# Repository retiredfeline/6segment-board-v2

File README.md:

# 6 segment 2 digit board, second version

These are the Kicad design files for the second version of the [6 segment 2 digit board](https://hackaday.io/project/175397-6-segment-2-digit-led-board) project, explained in a [log](https://hackaday.io/project/175396-6-segments-suffice/log/202924-6-segments-reloaded) for the original project. Changes have been made to the segment shapes to attempt to improve the font.

## Versioning

Release February 2022

## Authors

* **Ken Yap**

## License

See the [LICENSE](LICENSE.md) file for license rights and limitations (MIT).

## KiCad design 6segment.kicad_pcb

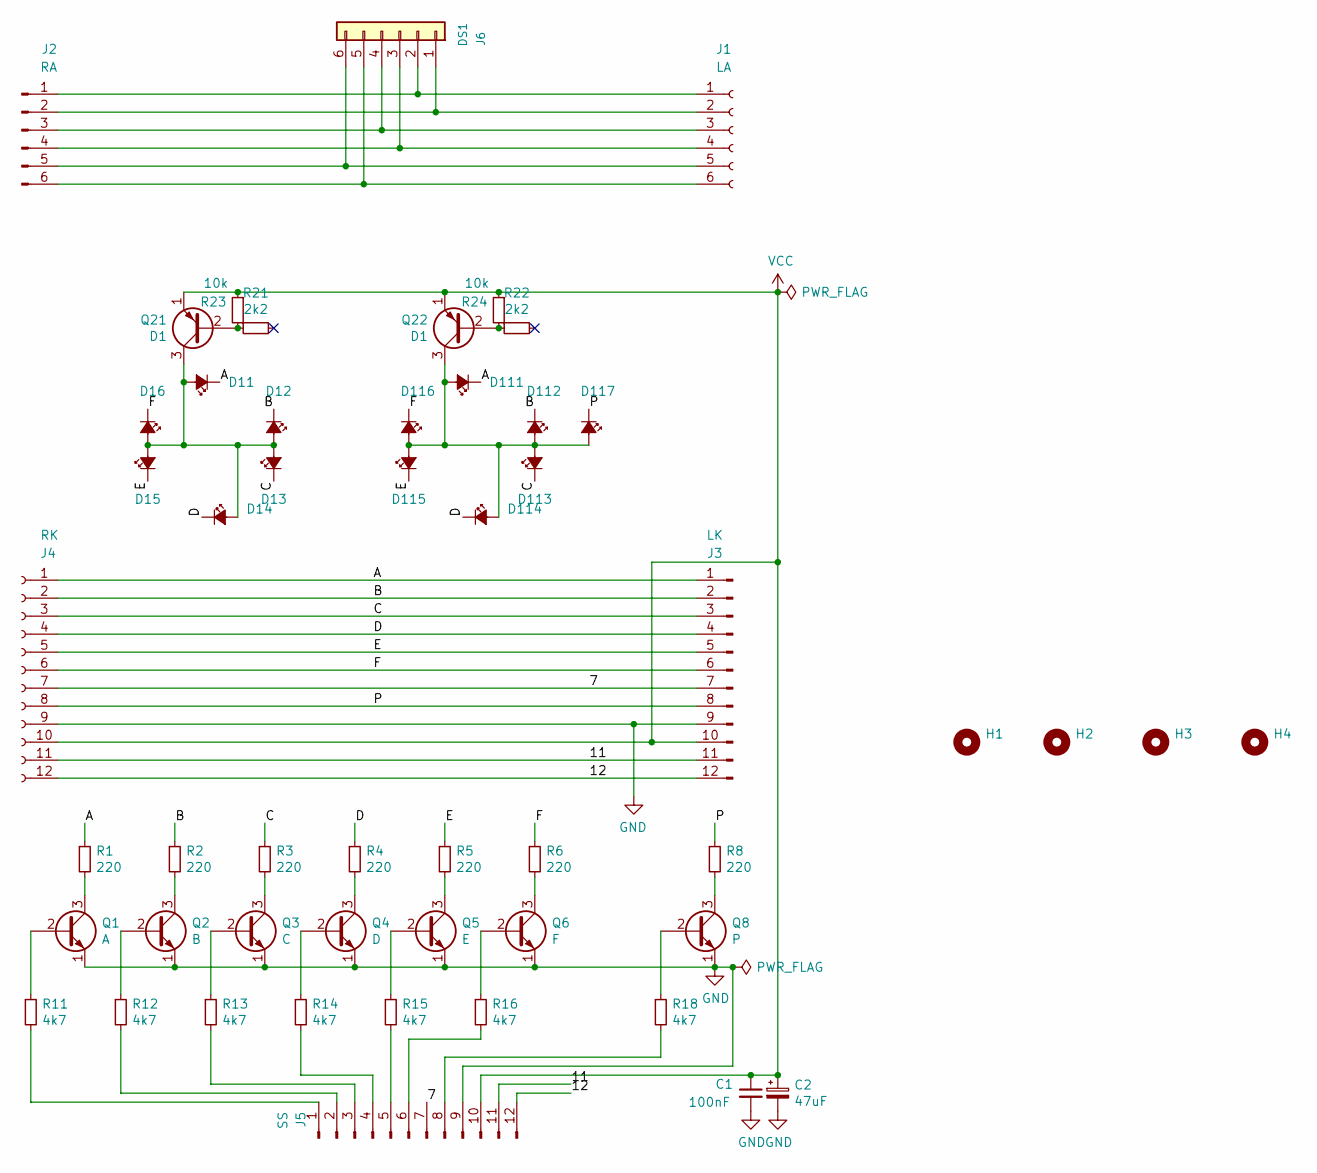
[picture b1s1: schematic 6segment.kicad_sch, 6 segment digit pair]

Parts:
C1: 100nF; C_Rect_L7.0mm_W2.0mm_P5.00mm
C2: 47uF; CP_Radial_D5.0mm_P2.50mm
D11, D111: A; LED_D3.0mmx4
D12, D112: B; LED_D3.0mmx4d
D13, D113: C; LED_D3.0mmx4kl
D14, D114: D; LED_D3.0mmx4
D15, D115: E; LED_D3.0mmx4d
D16, D116: F; LED_D3.0mmx4kl
D117: P; LED_D3.0mm-colon
H1, H2, H3, H4: MountingHole; MountingHole_3.5mm_Pad
J1: LA; PinSocket_1x06_P2.54mm_Horizontal
J2: RA; PinHeader_1x06_P2.54mm_Horizontal
J3: LK; PinSocket_1x12_P2.54mm_Horizontal
J4: RK; PinHeader_1x12_P2.54mm_Horizontal
J5: SS; PinHeader_1x12_P2.54mm_Vertical
J6: DS1; 2X3
Q1: A; TO-92
Q2: B; TO-92
Q3: C; TO-92
Q4: D; TO-92
Q5: E; TO-92
Q6: F; TO-92
Q8: P; TO-92
Q21, Q22: D1; TO-92
R1, R2, R3, R4, R5, R6, R8: 220; R_Axial_DIN0309_L9.0mm_D3.2mm_P12.70mm_Horizontal
R11, R12, R13, R14, R15, R16, R18: 4k7; R_Axial_DIN0309_L9.0mm_D3.2mm_P12.70mm_Horizontal
R21, R22: 2k2; R_Axial_DIN0207_L6.3mm_D2.5mm_P10.16mm_Horizontal
R23, R24: 10k; R_Axial_DIN0207_L6.3mm_D2.5mm_P10.16mm_Horizontal

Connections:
/7: J3.7, J4.7, J5.7
/11: J3.11, J4.11, J5.11
/12: J3.12, J4.12, J5.12
/A: D11.1 (K), D111.1 (K), J3.1, J4.1, R1.1
/B: D12.1 (K), D112.1 (K), J3.2, J4.2, R2.1
/C: D13.1 (K), D113.1 (K), J3.3, J4.3, R3.1
/D: D14.1 (K), D114.1 (K), J3.4, J4.4, R4.1
/E: D15.1 (K), D115.1 (K), J3.5, J4.5, R5.1
/F: D16.1 (K), D116.1 (K), J3.6, J4.6, R6.1
/P: D117.1 (K), J3.8, J4.8, R8.1
GND: C1.2, C2.2, J3.9, J4.9, J5.9, Q1.1 (E), Q2.1 (E), Q3.1 (E), Q4.1 (E), Q5.1 (E), Q6.1 (E), Q8.1 (E)
unnamed: D11.2 (A), D12.2 (A), D13.2 (A), D14.2 (A), D15.2 (A), D16.2 (A), Q21.3 (C)
unnamed: D111.2 (A), D112.2 (A), D113.2 (A), D114.2 (A), D115.2 (A), D116.2 (A), D117.2 (A), Q22.3 (C)
unnamed: J1.1, J2.1, J6.2
unnamed: J1.2, J2.2, J6.1
unnamed: J1.3, J2.3, J6.4
unnamed: J1.4, J2.4, J6.3
unnamed: J1.5, J2.5, J6.6
unnamed: J1.6, J2.6, J6.5
unnamed: J5.1, R11.2
unnamed: J5.2, R12.2
unnamed: J5.3, R13.2
unnamed: J5.4, R14.2
unnamed: J5.5, R15.2
unnamed: J5.6, R16.2
unnamed: J5.8, R18.2
unnamed: Q1.2 (B), R11.1
unnamed: Q1.3 (C), R1.2
unnamed: Q2.2 (B), R12.1
unnamed: Q2.3 (C), R2.2
unnamed: Q3.2 (B), R13.1
unnamed: Q3.3 (C), R3.2
unnamed: Q4.2 (B), R14.1
unnamed: Q4.3 (C), R4.2
unnamed: Q5.2 (B), R15.1
unnamed: Q5.3 (C), R5.2
unnamed: Q6.2 (B), R16.1
unnamed: Q6.3 (C), R6.2
unnamed: Q8.2 (B), R18.1
unnamed: Q8.3 (C), R8.2
unnamed: Q21.2 (B), R21.1, R23.2
unnamed: Q22.2 (B), R22.1, R24.2
VCC: C1.1, C2.1, J3.10, J4.10, J5.10, Q21.1 (E), Q22.1 (E), R23.1, R24.1

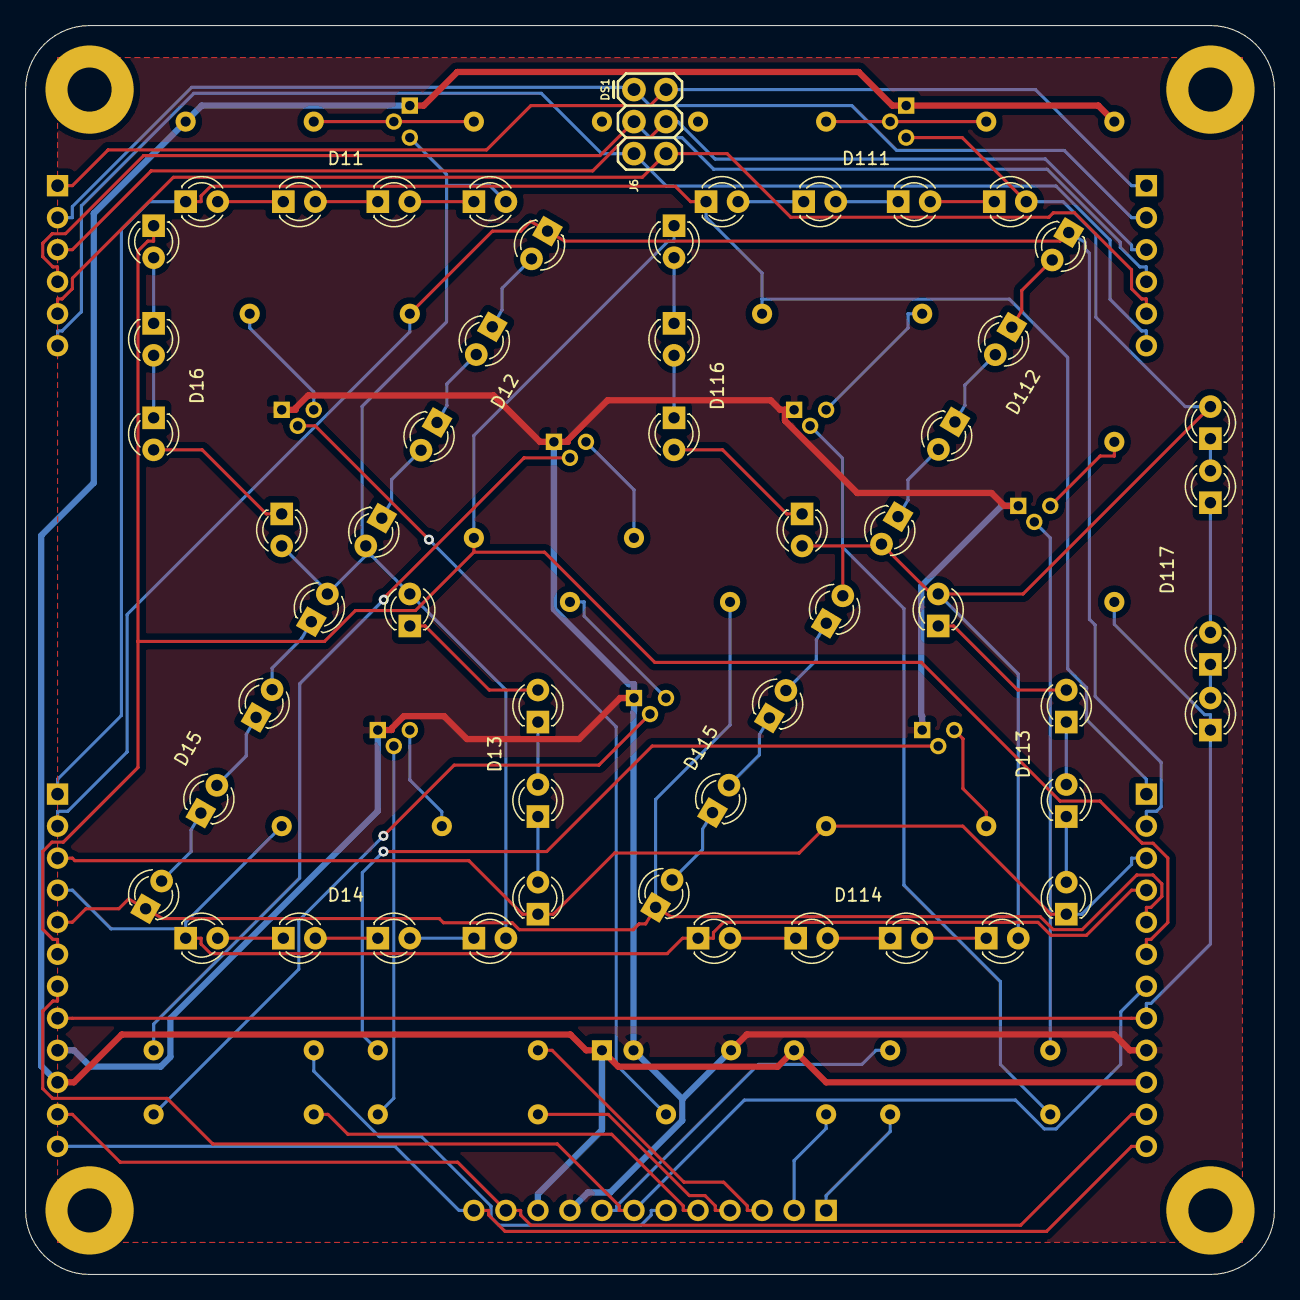
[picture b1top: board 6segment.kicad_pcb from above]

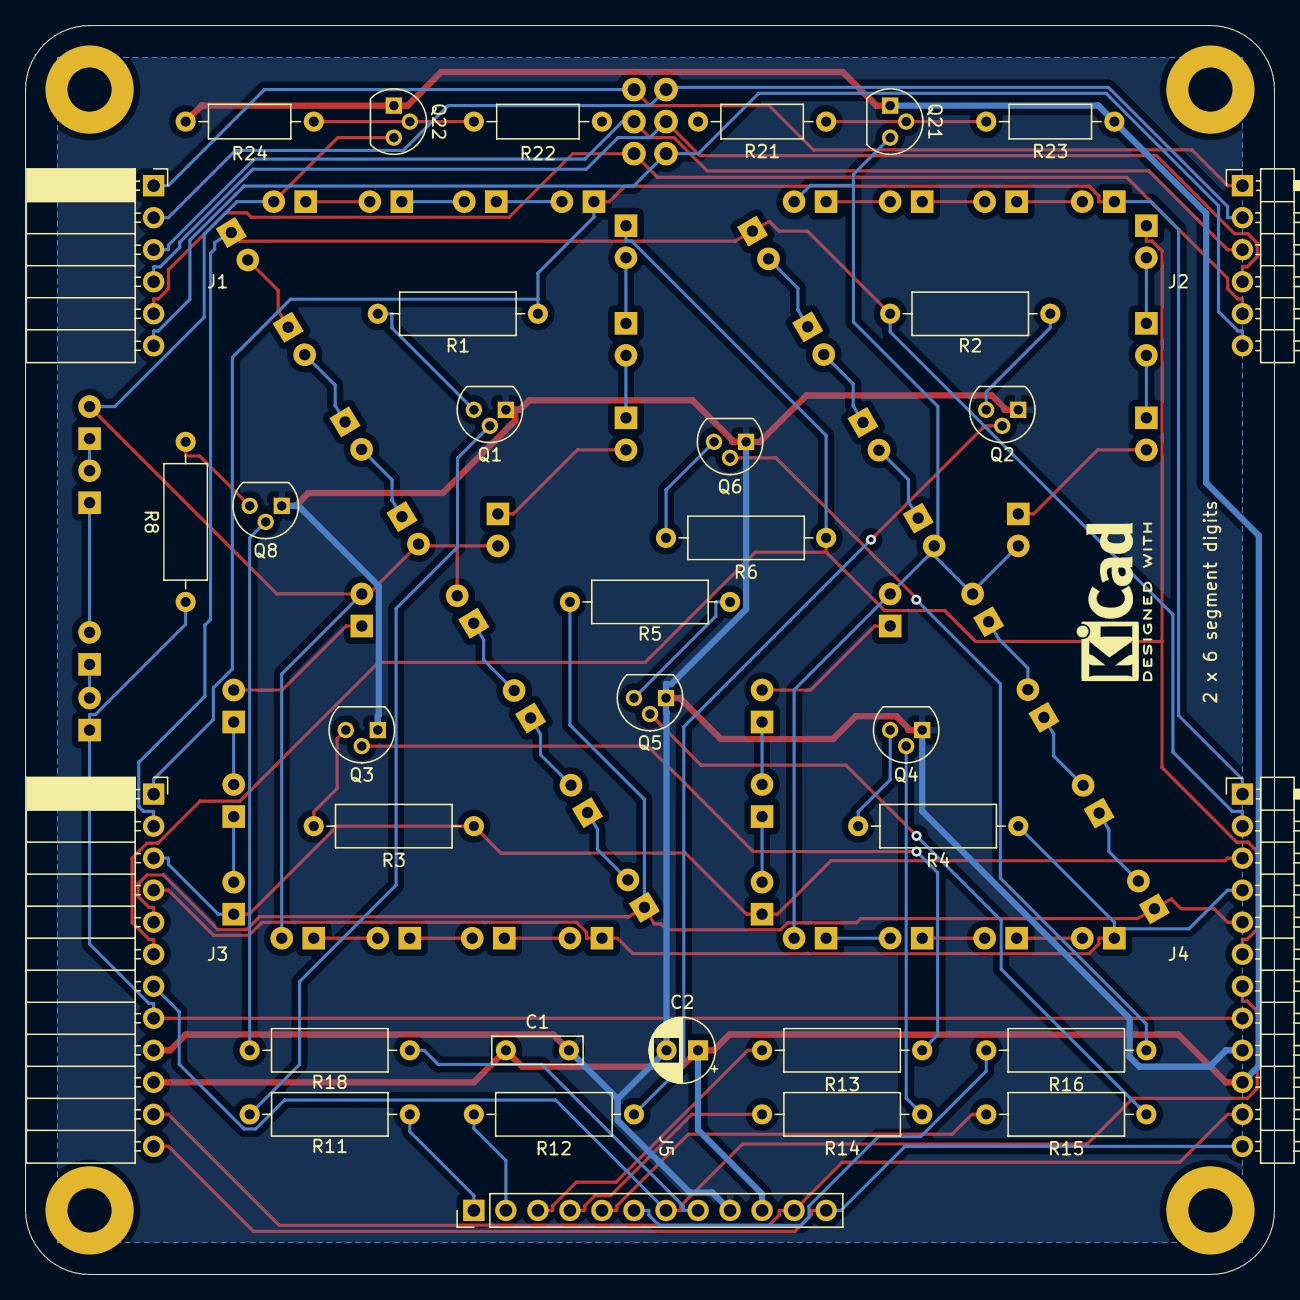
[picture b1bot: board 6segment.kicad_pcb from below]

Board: 2 copper layers, 99.1 x 99.1 mm, 52 parts (34 on the bottom side), 43 nets.

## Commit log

2021-12-23 Released version
2022-02-05 Link to project log
2025-02-23 Update to KiCad v8
